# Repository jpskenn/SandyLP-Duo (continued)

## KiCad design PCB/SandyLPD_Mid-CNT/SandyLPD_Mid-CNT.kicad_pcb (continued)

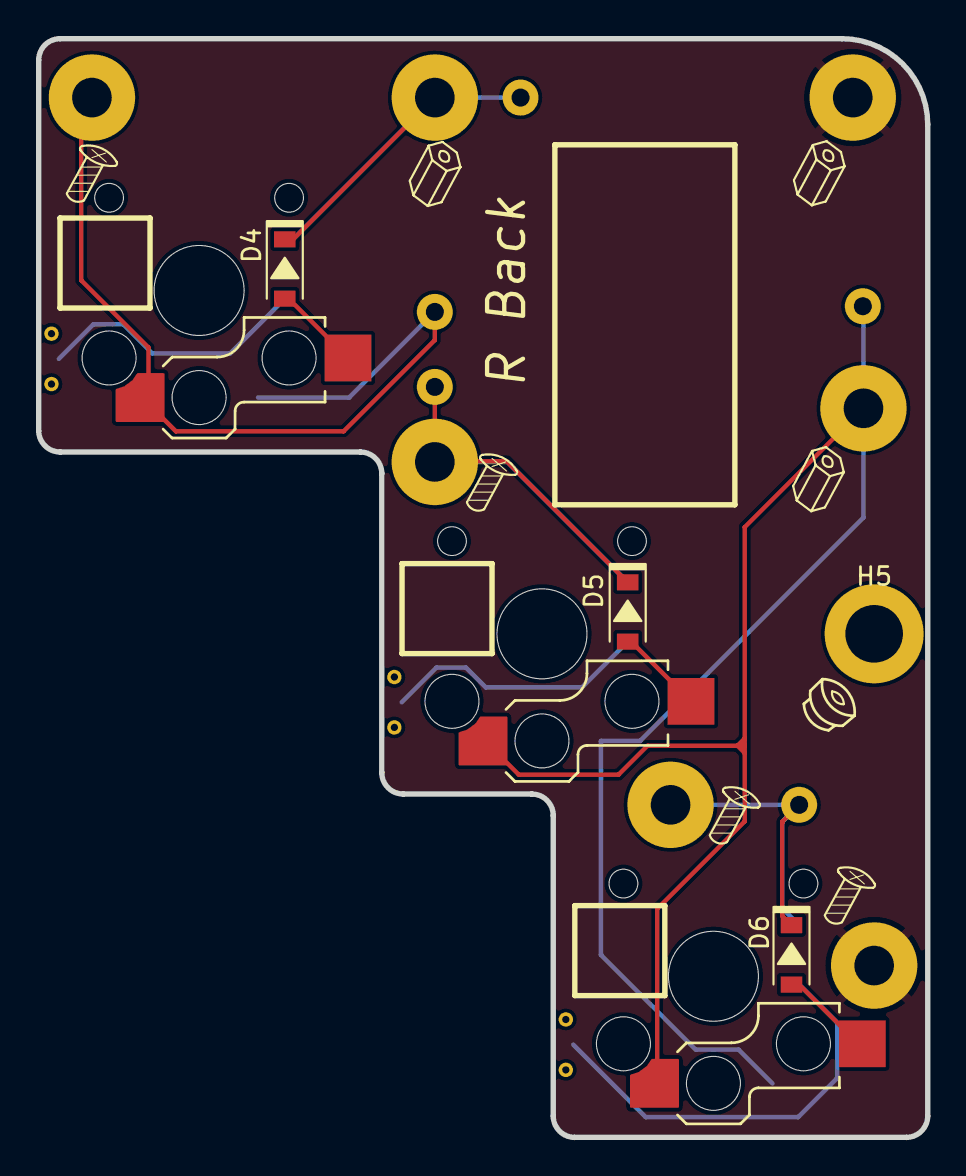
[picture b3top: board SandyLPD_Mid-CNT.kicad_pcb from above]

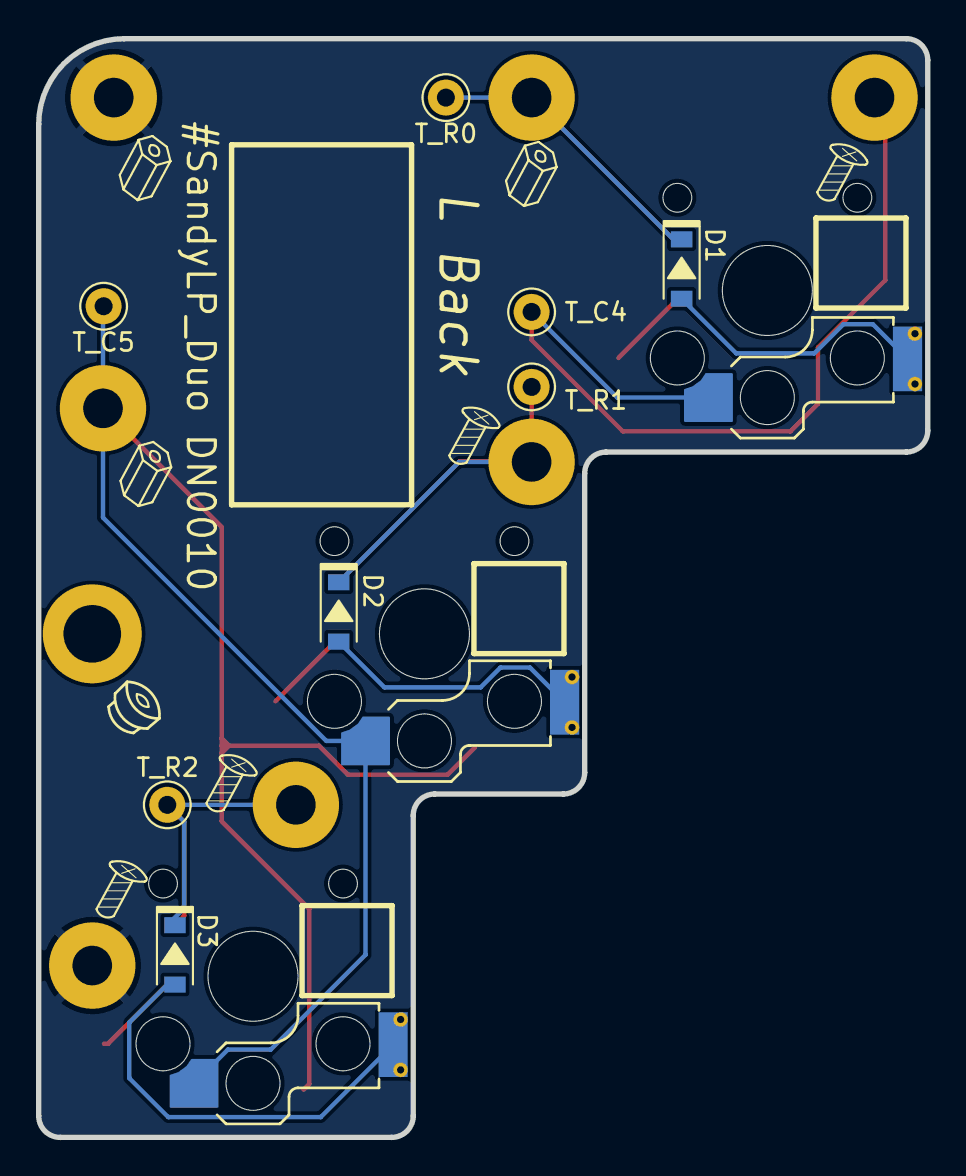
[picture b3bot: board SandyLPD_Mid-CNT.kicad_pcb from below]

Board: 2 copper layers, 49.4 x 61.0 mm, 26 parts (11 on the bottom side), 12 nets.

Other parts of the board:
Cutout1: 60_Outline; SandyLPD_outline_Mid-CNT

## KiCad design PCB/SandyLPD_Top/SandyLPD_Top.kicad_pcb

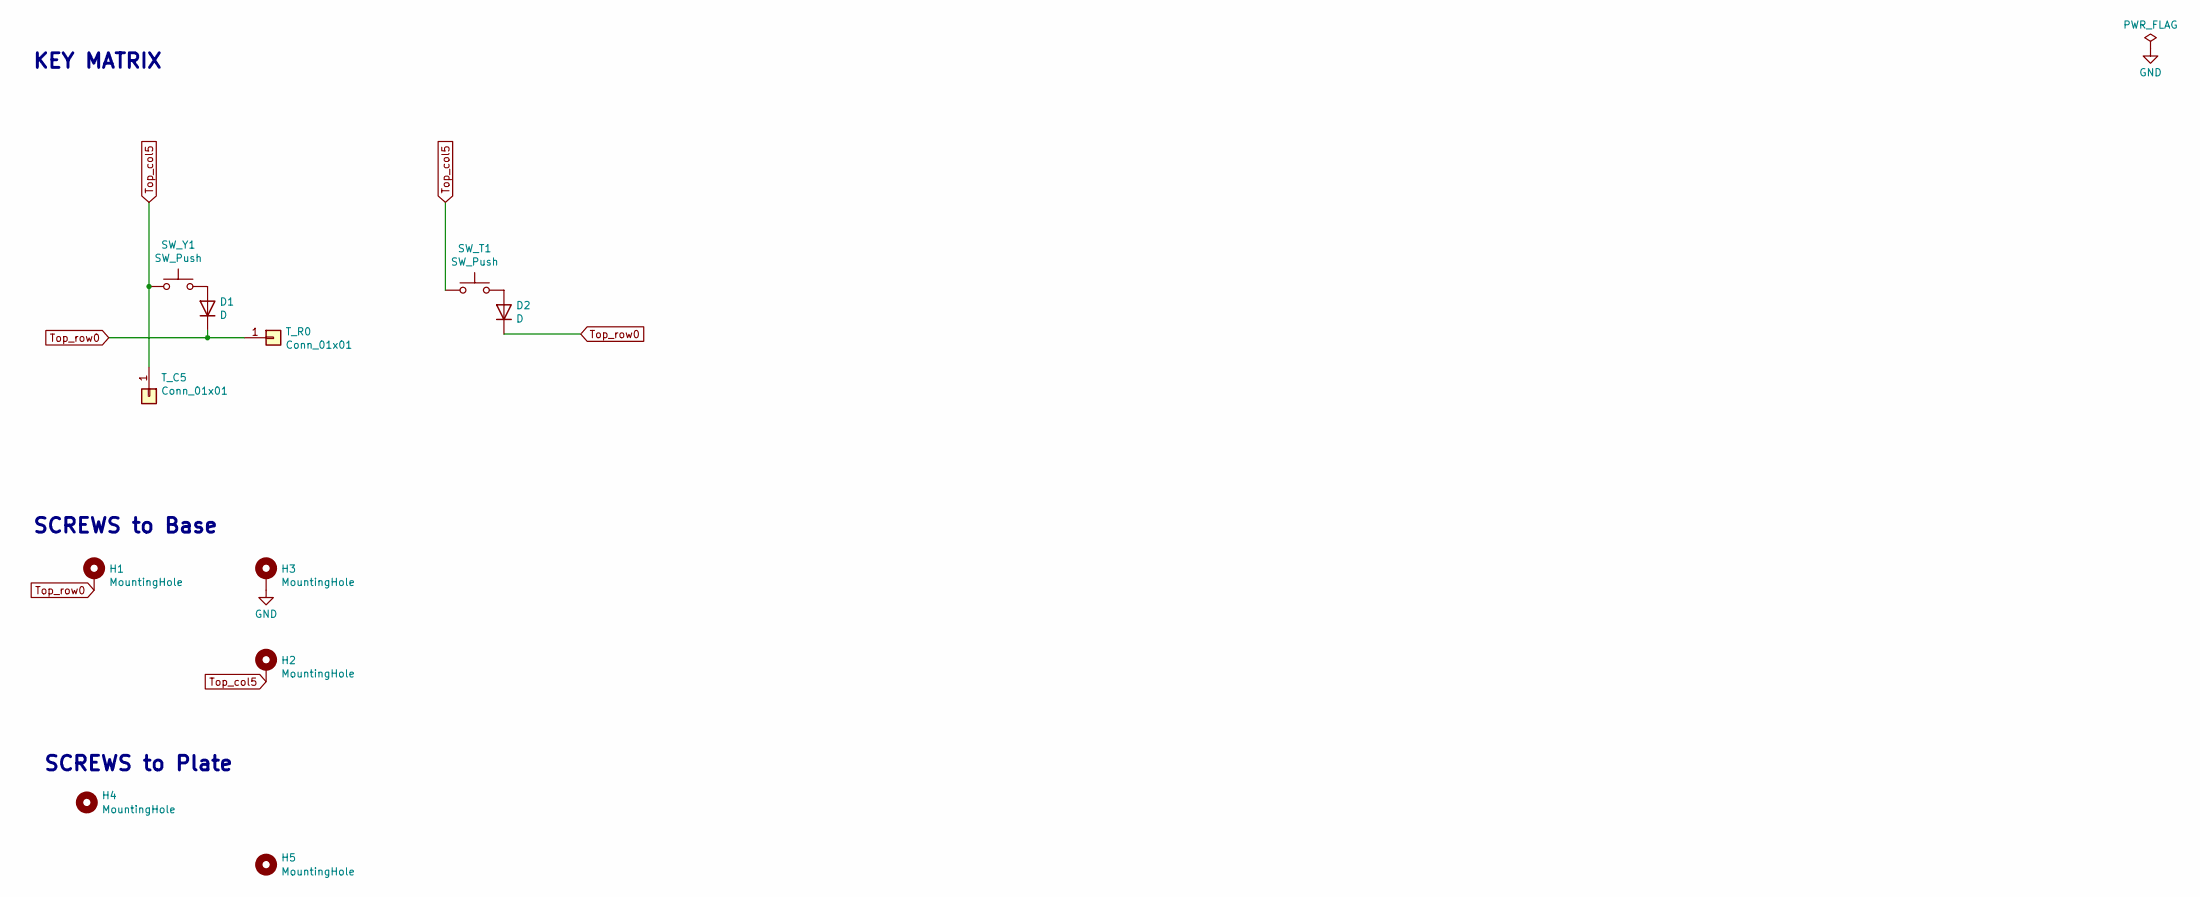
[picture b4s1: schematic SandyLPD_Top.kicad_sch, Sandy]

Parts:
D1, D2: D; D_SOD-123_Emphasized_Direction_Line; LCSC C81598
H1, H2, H3: MountingHole; MountingHole_2.2mm_M2_Pad_minimal_L8mm_SlimHead_L3.5mm_Spac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
H4, H5: MountingHole; MountingHole_M2_Through-hole_tap_THC-0.8-1.0-2
SW_T1: SW_Push; Kailh_socket_ChocV2_for_Reverse
SW_Y1: SW_Push; Kailh_socket_ChocV2_small_#2pad_for_Reverse_no_hole
T_C5: Conn_01x01; TestPoint_THTPad_D2.0mm_Drill1.0mm
T_R0: Conn_01x01; TestPoint_THTPad_D2.0mm_Drill1.0mm

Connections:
GND: H3.1
unnamed: D1.2 (A), SW_Y1.2
unnamed: D2.2 (A), SW_T1.2
Top_col5: H2.1, SW_T1.1, SW_Y1.1, T_C5.1
Top_row0: D1.1 (K), D2.1 (K), H1.1, T_R0.1

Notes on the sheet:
SCREWS to Plate
KEY MATRIX
SCREWS to Base

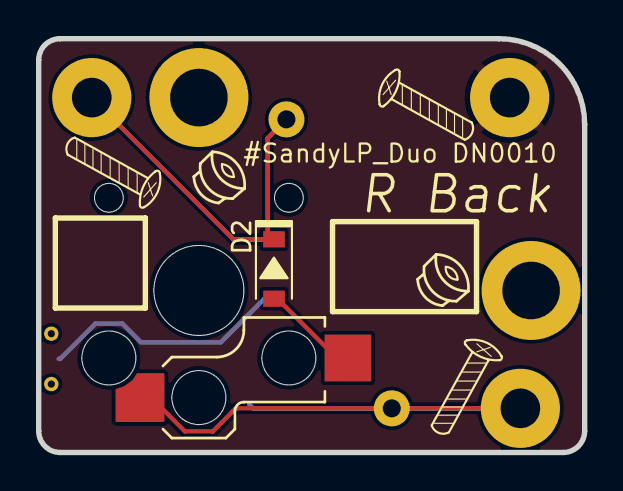
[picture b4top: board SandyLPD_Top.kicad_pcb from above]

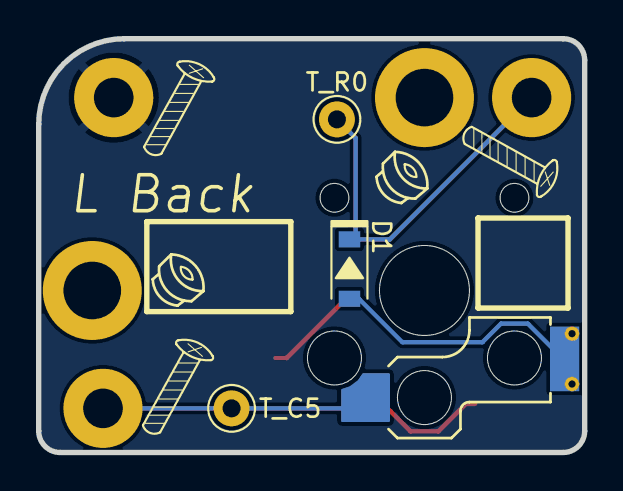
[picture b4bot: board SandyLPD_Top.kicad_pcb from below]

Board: 2 copper layers, 30.3 x 23.0 mm, 11 parts (4 on the bottom side), 4 nets.

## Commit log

2024-12-11 SandyLPを元に書き始めた
2024-12-12 SandyLPからBaseをコピー。RP2040-Zeroテスト中。
2024-12-12 TRRSジャック確認
2024-12-14 TRRSとRP2040-Zeroを追加
2024-12-14 回路図作成中。RP2040-Zero等不要ファイル削除。
2024-12-14 Base基板 ネジ穴仮配置
2024-12-15 Base基板 MCUまわりの配置検討
2024-12-16 スルーホールタップ等を盛り込み
2024-12-16 ネジ位置調整中
2024-12-19 スルーホールタップ位置確認。Base基板外形を左右へ拡大。
2024-12-19 ネジ位置決定のつもり
2024-12-19 とりあえずMCUまわりに配線できることを確認
2024-12-20 MCU使用ピンを仮決め中
2024-12-20 フラッシュメモリの部品置き換わりを修正
2024-12-20 仮配線中
2024-12-20 ボトムプレートの穴あけに向け、パーツ位置調整中。
2024-12-21 LED、WS2812Cはパスコン不要のため、仮想パーツとして実際には配置しない。
2024-12-21 パーツ配置調整中
2024-12-21 左手のパーツ配置と配線、一旦完了。
2024-12-21 ボトムA作成
2024-12-21 基板外側のボトム用ネジ位置を変更 #18
2024-12-21 ボトムプレートB追加
2024-12-21 ボトムプレートの左右幅調整 #18
2024-12-22 Mid-ISO追加
2024-12-22 Mid中央追加。調整中。外形なども含めまだまだ。
2024-12-22 Base→MId中央のネジ位置を1箇所変更
    Mid中央をリバーシブルにすると、ソケットのパッドと干渉が出たため。
2024-12-22 Mid中央プレート用のネジ穴位置調整
2024-12-22 Mid中央、配線やシルク調整中。
2024-12-22 未使用ファイル削除
2024-12-22 パーツ配置完了。ネジ位置調整中。
2024-12-22 スルーホールタップの接続先を変更・調整 #19
2024-12-22 不要ファイル削除
2024-12-22 Top基板追加
2024-12-22 シルク調整
2024-12-22 Mid-ISO用スイッチプレート追加
2024-12-22 Top用スイッチプレート追加
2024-12-22 不要コメント削除
2024-12-22 WIP Mid-CNT用スイッチプレート追加。穴サイズ調整中。
2024-12-22 WIP Top基板裏側のソケットを逃す穴を作成中。
2024-12-22 WIP Top基板うら側のソケットを逃がす穴に調整中
2024-12-23 Top基板裏側のソケットを逃す穴を作成
2024-12-23 WIP 基板Base 右手MCUまわりを配置中
2024-12-24 右手MCUまわりの配置中
2024-12-24 WIP 右手MCUまわりを配置中
2024-12-24 リセットスイッチ穴追加。USBまわり少し拡大
2024-12-24 ソケット逃し穴の形状を変更
2024-12-24 EC11Kサポート廃止（新規設計非推奨のため）
2024-12-25 右手スピーカーの位置を調整
2024-12-25 基板Base右手側 配線中
2024-12-25 右手配線ほぼ完了 全体調整中
2024-12-25 WIP 配線調整
2024-12-25 配線ひとまず完了
2024-12-25 配線調整
2024-12-25 ゴムシート貼り付け位置を準備中
2024-12-26 ビルドガイドをユーザーズマニュアルに変えて、少しずつ書き始め。
2024-12-27 製作過程を追記中
2024-12-27 LEDをJLCPCBのBasic Partsに変更
2024-12-27 #32 DIPスイッチにLEDのON/OFFを接続
2024-12-27 シルク表示を調整
2025-01-01 ボトムプレートの穴を大きく
2025-01-01 電源LED位置調整。ボトムA,Bのリセット穴サイズ変更。Fusion用STEP出力。
2025-01-01 Base用スイッチプレートを作り始め
2025-01-01 WIP Base用スイッチプレートの外形
2025-01-01 外形調整
2025-01-01 LED窓、LED位置調整
2025-01-01 基板Top裏側のパーツ逃し穴を調整
2025-01-01 不要アイコン削除
2025-01-01 ゴムシート貼り付け位置をシルク入れている
2025-01-02 ネジ穴にスルーホールタップのアイコンを追加
2025-01-02 ゴムシート貼り付け指標をわかりやすく。不要なシルクを非表示に。
2025-01-02 間違い防止のシルク #30
2025-01-02 部品は位置調整
2025-01-02 フォーマット
2025-01-02 ダイオードの番号を調整
2025-01-02 LEDの取り付け指標を追加
2025-01-02 ゴムシート貼り付け指標を調整
2025-01-02 基板に合わせて説明を調整
2025-01-02 不要部品削除
2025-01-02 Mid、Topの外形を微調整
2025-01-02 プレート固定用ネジの3Dモデルを追加
2025-01-03 組み合わせるところまで
2025-01-03 パーツ等追記
2025-01-03 VIA打ち
2025-01-03 DIPスイッチを調整
2025-01-03 WIP ボトムプレートへの記載を試し中
2025-01-03 DIPスイッチのシルク追加
2025-01-04 シルク追加
2025-01-04 ボトムプレートの外形を、基板Baseと同形状に戻す。
    仕様では左右端を斜めにして、テント時の小指側持ち上がりを防止する予定だった。
    しかし、ケースなどを考慮すると、ボトムの外形が異なると不都合なため、基板Baseと同形状とする。
2025-01-04 リセットスイッチ、電源LEDの位置を、左右で合わせてボトムBの切り欠きに収まるように調整。
2025-01-04 シルク位置調整 #20
2025-01-04 ロータリーエンコーダの穴をちょっと小さく。 #40
2025-01-04 USBコネクタのアイコン表記 #30
2025-01-04 ゴムシート貼り付けめやすを追加
2025-01-05 Mid-CNTのプレート固定用スルーホールタップを1個減らす
2025-01-05 スイッチにネジ頭がかかるため、基板Baseと基板Mid-CNTを接続するネジ位置を調整。
2025-01-05 ネジの3Dモデル追加
2025-01-05 ネジの3Dモデルの向きを反転
2025-01-05 3Dモデルのネジの長さが不正だったので、別のモデルに変更。
2025-01-05 ネジ等の3Dモデル追加
2025-01-05 USBコネクタの切り欠きが大きすぎたので小さく。 #47
2025-01-05 DIPスイッチ取り付け前に通電確認できるジャンパを追加。 #42
2025-01-05 QRコード、ロゴ追加
2025-01-05 スローガン記入 #48
2025-01-06 ロータリーエンコーダとボトムBの干渉回避、ネジ本数など #27
2025-01-07 ヒューズをResettableに変更
2025-01-07 WIP ショットキーダイオードを置き換え中
2025-01-07 WIP パーツ配置、配線中
2025-01-08 WIP 配線中。左手はよさそうかも？
2025-01-08 WIP 配線中。
2025-01-08 WIP パーツ配置、配線中。ボトムAの逃し穴に合わせて、少し移動。
2025-01-08 WIP 左手を右手に合わせて回転した
2025-01-09 ひとまず、逆流防止の回路完成
2025-01-09 部品逃がし穴の位置とサイズを調整
2025-01-09 ネジ穴位置を再調整。
2025-01-10 WIP BaseにESDとヒューズ追加。ボトムAの穴位置調整中。
2025-01-10 USBコネクタの3Dモデルのずれ修正。
2025-01-10 穴位置調整。ざっくりOK。
2025-01-10 原点リセット
2025-01-10 穴位置調整
